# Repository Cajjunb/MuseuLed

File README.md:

# PCB Circuit Specification

## Description
The PCB Circuit Specification project aims to provide detailed specifications and guidelines for designing printed circuit boards (PCBs). This project covers various aspects of PCB design, including component placement, trace routing, and manufacturing considerations. The project is for a Computer Vision application and for the #ART15 fair of computer art.

## Features
- Comprehensive guidelines for PCB component placement
- Detailed trace routing specifications
- Design rules for ensuring signal integrity and minimizing noise
- Manufacturing considerations and best practices
- Sample PCB designs and case studies for reference

## Requirements
- PCB design software (e.g., Eagle, Altium Designer)
- Understanding of electronic components and circuit design principles
- Knowledge of PCB manufacturing processes

## Credits
This project is maintained by Leandro Ramalho Motta Ferreira. If you have any questions or inquiries, please contact [cajjunb@gmail.com].

## License
This project is licensed under the [MIT License](LICENSE)

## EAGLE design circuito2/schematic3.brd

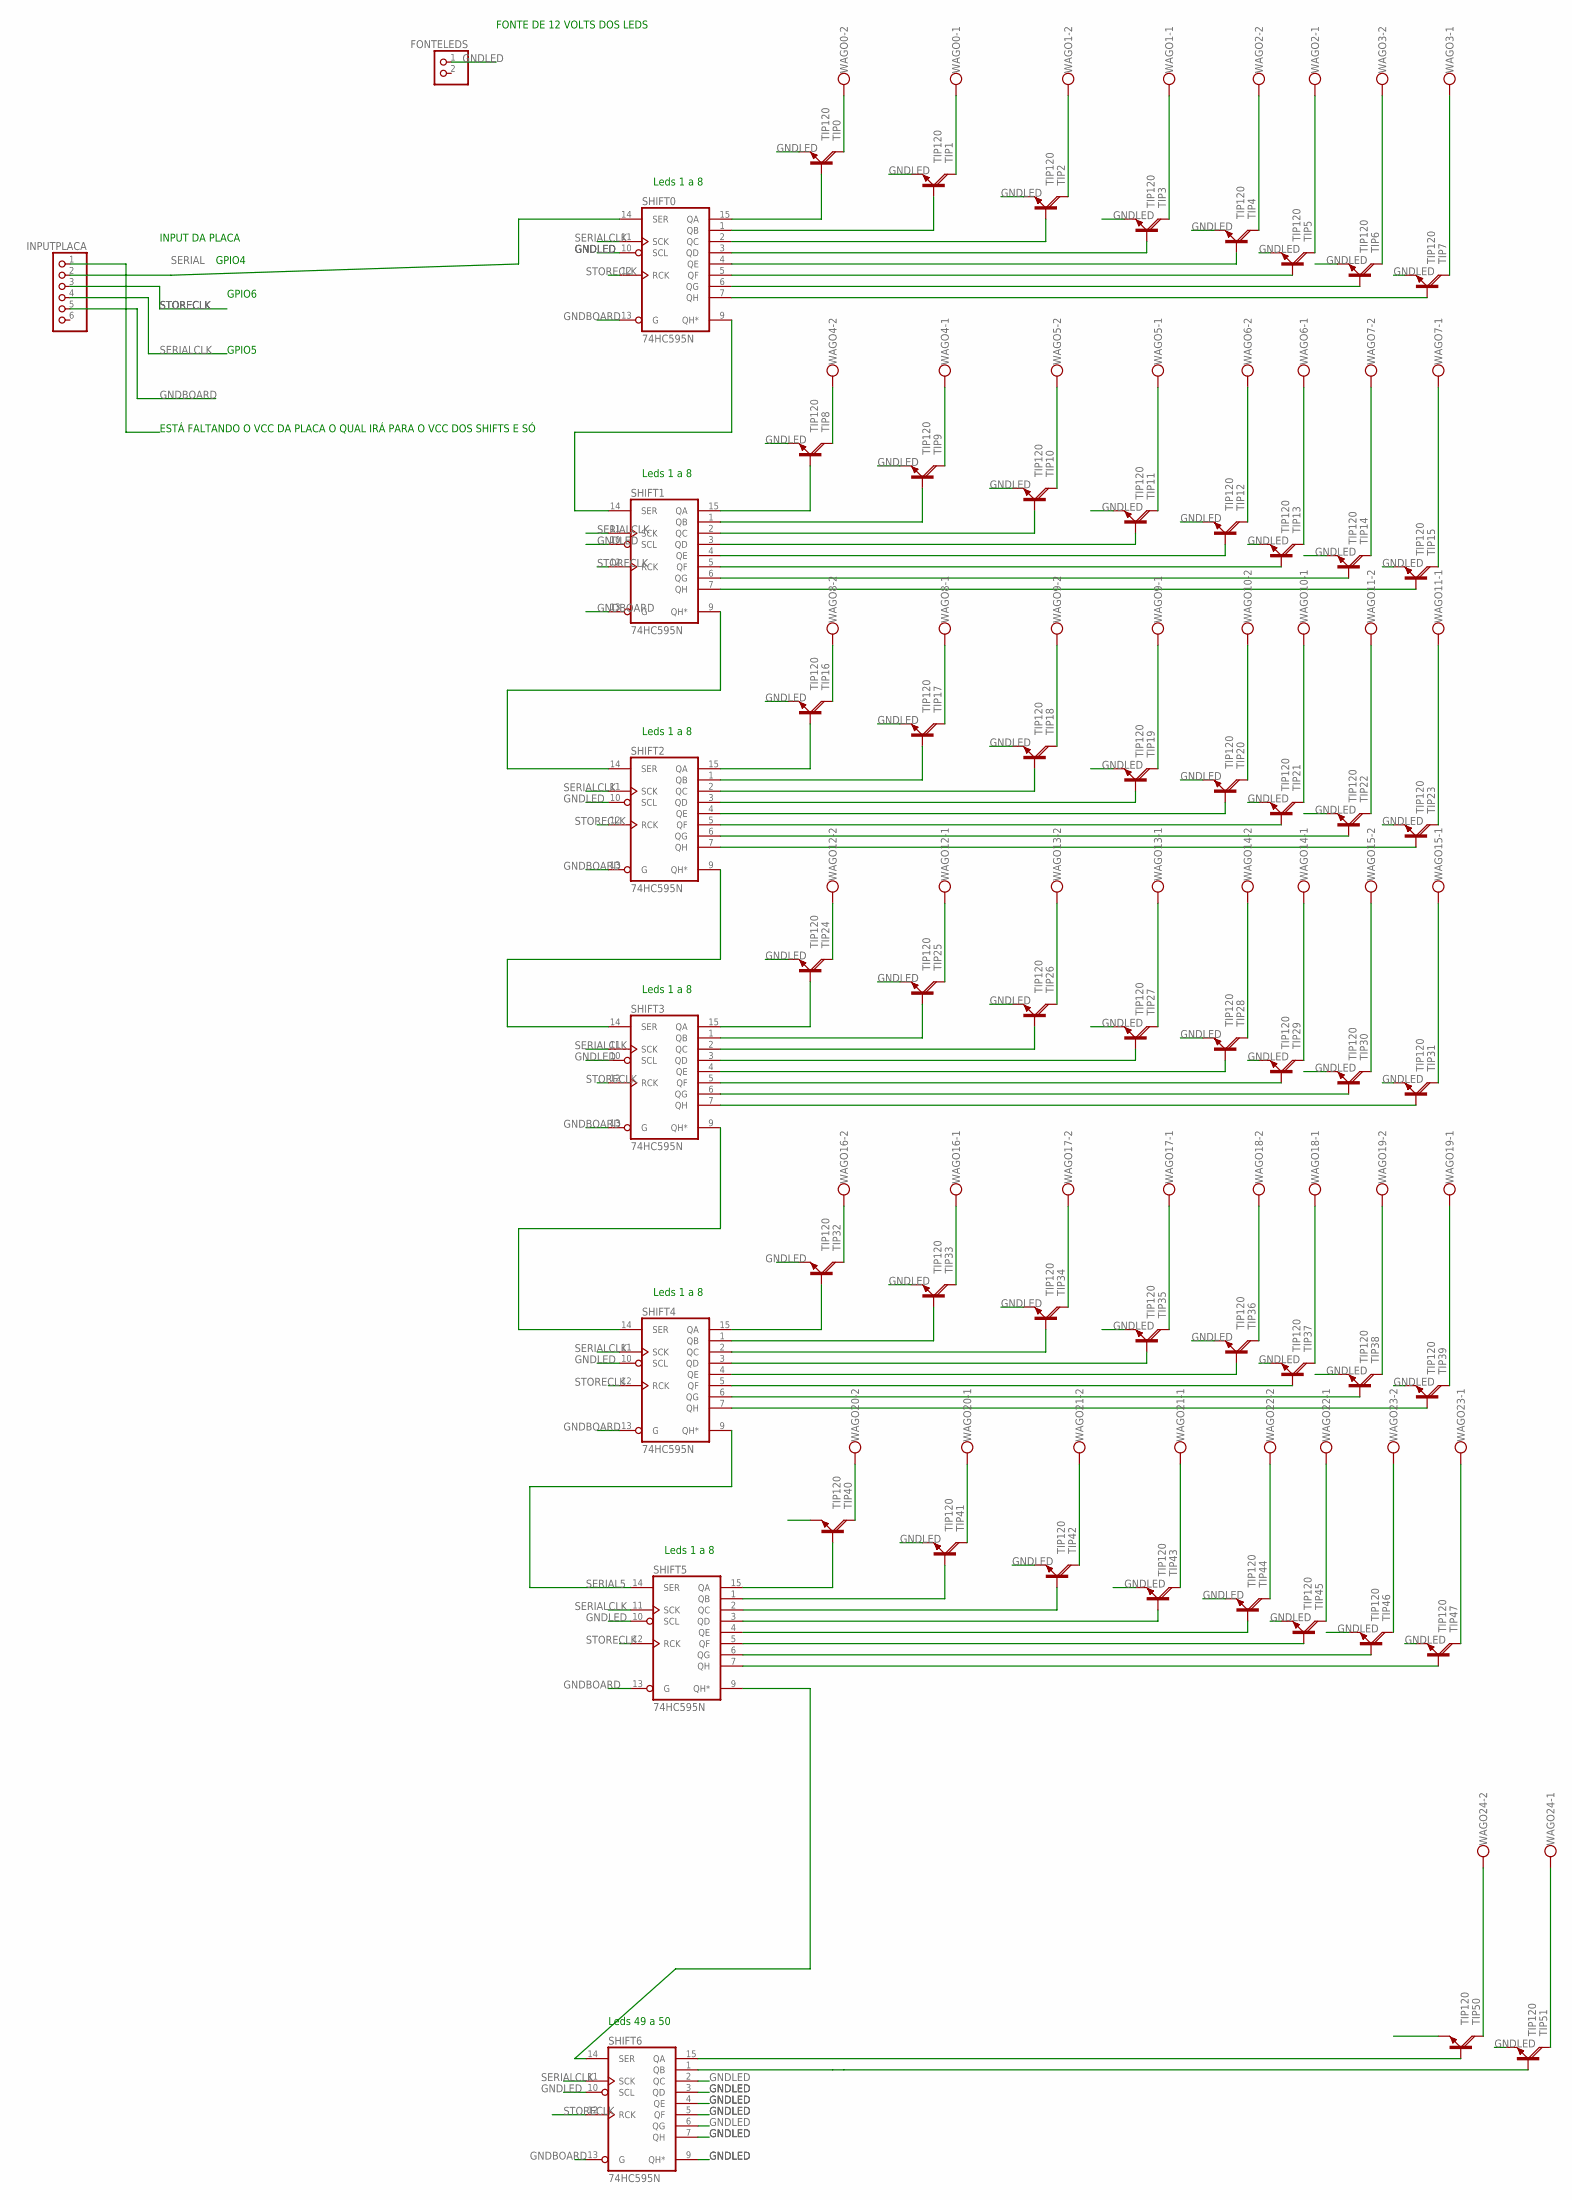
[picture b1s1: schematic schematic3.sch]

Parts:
FONTELEDS: PINHD-1X2; 1X02
INPUTPLACA: PINHD-1X6; 1X06
SHIFT0, SHIFT1, SHIFT2, SHIFT3, SHIFT4, SHIFT5, SHIFT6: 74HC595N; DIL16
TIP0, TIP1, TIP2, TIP3, TIP4, TIP5, TIP6, TIP7, TIP8, TIP9, TIP10, TIP11, TIP12, TIP13, TIP14, TIP15, TIP16, TIP17, TIP18, TIP19, TIP20, TIP21, TIP22, TIP23, TIP24, TIP25, TIP26, TIP27, TIP28, TIP29, TIP30, TIP31, TIP32, TIP33, TIP34, TIP35, TIP36, TIP37, TIP38, TIP39, TIP40, TIP41, TIP42, TIP43, TIP44, TIP45, TIP46, TIP47, TIP50, TIP51: TIP120; TO220AH
WAGO0, WAGO1, WAGO2, WAGO3, WAGO4, WAGO5, WAGO6, WAGO7, WAGO8, WAGO9, WAGO10, WAGO11, WAGO12, WAGO13, WAGO14, WAGO15, WAGO16, WAGO17, WAGO18, WAGO19, WAGO20, WAGO21, WAGO22, WAGO23, WAGO24: W237-102

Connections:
unnamed: SHIFT0.15 (QA), TIP0.B
unnamed: SHIFT0.1 (QB), TIP1.B
unnamed: SHIFT0.2 (QC), TIP2.B
unnamed: SHIFT0.3 (QD), TIP3.B
unnamed: SHIFT0.4 (QE), TIP4.B
unnamed: SHIFT0.5 (QF), TIP5.B
unnamed: SHIFT0.6 (QG), TIP6.B
unnamed: SHIFT0.7 (QH), TIP7.B
unnamed: SHIFT1.15 (QA), TIP8.B
unnamed: SHIFT1.1 (QB), TIP9.B
unnamed 11: SHIFT6.15 (QA), TIP50.B; also elsewhere on the board
unnamed: SHIFT1.2 (QC), TIP10.B
unnamed: SHIFT4.5 (QF), TIP37.B
unnamed: SHIFT1.3 (QD), TIP11.B
unnamed: SHIFT1.4 (QE), TIP12.B
unnamed: SHIFT4.6 (QG), TIP38.B
unnamed: SHIFT1.5 (QF), TIP13.B
unnamed: SHIFT4.7 (QH), TIP39.B
unnamed: SHIFT1.6 (QG), TIP14.B
unnamed: SHIFT5.5 (QF), TIP45.B
unnamed: SHIFT1.7 (QH), TIP15.B
unnamed: TIP8.C, WAGO4.2
unnamed: TIP9.C, WAGO4.1
unnamed: TIP10.C, WAGO5.2
unnamed: TIP11.C, WAGO5.1
unnamed: TIP12.C, WAGO6.2
unnamed: TIP13.C, WAGO6.1
unnamed: TIP14.C, WAGO7.2
unnamed: TIP15.C, WAGO7.1
unnamed: SHIFT2.15 (QA), TIP16.B
unnamed: SHIFT2.1 (QB), TIP17.B
unnamed: SHIFT2.2 (QC), TIP18.B
unnamed: SHIFT2.3 (QD), TIP19.B
unnamed: SHIFT2.4 (QE), TIP20.B
unnamed: SHIFT2.5 (QF), TIP21.B
unnamed: SHIFT2.6 (QG), TIP22.B
unnamed: SHIFT2.7 (QH), TIP23.B
unnamed: TIP16.C, WAGO8.2
unnamed: TIP17.C, WAGO8.1
unnamed: TIP18.C, WAGO9.2
unnamed: TIP19.C, WAGO9.1
unnamed: TIP20.C, WAGO10.2
unnamed: TIP21.C, WAGO10.1
unnamed: SHIFT4.15 (QA), TIP32.B
unnamed: TIP23.C, WAGO11.1
unnamed: SHIFT3.15 (QA), TIP24.B
unnamed: SHIFT3.1 (QB), TIP25.B
unnamed: SHIFT3.2 (QC), TIP26.B
unnamed: SHIFT3.3 (QD), TIP27.B
unnamed: SHIFT3.4 (QE), TIP28.B
unnamed: SHIFT5.6 (QG), TIP46.B
unnamed: SHIFT5.7 (QH), TIP47.B
unnamed: TIP0.C, WAGO0.2
unnamed: SHIFT3.5 (QF), TIP29.B
unnamed: SHIFT3.6 (QG), TIP30.B
unnamed: SHIFT3.7 (QH), TIP31.B
unnamed: TIP24.C, WAGO12.2
unnamed: TIP25.C, WAGO12.1
unnamed: TIP26.C, WAGO13.2
unnamed: SHIFT4.1 (QB), TIP33.B
unnamed: SHIFT4.2 (QC), TIP34.B
unnamed: SHIFT5.9 (QH*), SHIFT6.14 (SER)
unnamed: TIP29.C, WAGO14.1
unnamed: TIP30.C, WAGO15.2
unnamed: TIP31.C, WAGO15.1
unnamed: SHIFT4.3 (QD), TIP35.B
unnamed: SHIFT4.4 (QE), TIP36.B
unnamed: TIP1.C, WAGO0.1
unnamed: TIP2.C, WAGO1.2
unnamed: TIP32.C, WAGO16.2
unnamed: TIP3.C, WAGO1.1
unnamed: TIP33.C, WAGO16.1
unnamed: TIP34.C, WAGO17.2
unnamed: TIP37.C, WAGO18.1
unnamed: TIP38.C, WAGO19.2
unnamed: TIP39.C, WAGO19.1
unnamed: SHIFT5.15 (QA), TIP40.B
unnamed: SHIFT5.1 (QB), TIP41.B
unnamed: SHIFT5.2 (QC), TIP42.B
unnamed: SHIFT5.3 (QD), TIP43.B
unnamed: SHIFT5.4 (QE), TIP44.B
unnamed: TIP40.C, WAGO20.2
unnamed: TIP41.C, WAGO20.1
unnamed: TIP42.C, WAGO21.2
unnamed: TIP45.C, WAGO22.1
unnamed: TIP46.C, WAGO23.2
unnamed: TIP47.C, WAGO23.1
unnamed 88: TIP50.C, WAGO24.2; also elsewhere on the board
unnamed 89: TIP51.C, WAGO24.1; also elsewhere on the board
unnamed 90: SHIFT6.1 (QB), TIP51.B; also elsewhere on the board
unnamed: TIP4.C, WAGO2.2
unnamed: TIP5.C, WAGO2.1
unnamed: TIP6.C, WAGO3.2
unnamed: TIP7.C, WAGO3.1
SERIAL: INPUTPLACA.2, SHIFT0.14 (SER)
SERIAL1: SHIFT0.9 (QH*), SHIFT1.14 (SER)
SERIAL2: SHIFT1.9 (QH*), SHIFT2.14 (SER)
SERIAL3: SHIFT2.9 (QH*), SHIFT3.14 (SER)
SERIAL4: SHIFT3.9 (QH*), SHIFT4.14 (SER)
SERIAL5: SHIFT4.9 (QH*), SHIFT5.14 (SER)
SERIALCLK: INPUTPLACA.4, SHIFT0.11 (SCK), SHIFT1.11 (SCK), SHIFT2.11 (SCK), SHIFT3.11 (SCK), SHIFT4.11 (SCK), SHIFT5.11 (SCK), SHIFT6.11 (SCK)
STORECLK: INPUTPLACA.3, SHIFT0.12 (RCK), SHIFT1.12 (RCK), SHIFT2.12 (RCK), SHIFT3.12 (RCK), SHIFT4.12 (RCK), SHIFT5.12 (RCK), SHIFT6.12 (RCK)
VCC: INPUTPLACA.1, SHIFT0.16 (VCC), SHIFT1.16 (VCC), SHIFT2.16 (VCC), SHIFT3.16 (VCC), SHIFT4.16 (VCC), SHIFT5.16 (VCC), SHIFT6.16 (VCC)
WAGO1: TIP35.C, WAGO17.1
WAGO2: TIP36.C, WAGO18.2
WAGO3: TIP43.C, WAGO21.1
WAGO4: TIP44.C, WAGO22.2
WAGO11: TIP22.C, WAGO11.2
WAGO14: TIP27.C, WAGO13.1
WAGO15: TIP28.C, WAGO14.2

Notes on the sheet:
Leds 1 a 8
Leds 49 a 50
FONTE DE 12 VOLTS DOS LEDS
INPUT DA PLACA
ESTÁ FALTANDO O VCC DA PLACA O QUAL IRÁ PARA O VCC DOS SHIFTS E SÓ
GPIO4
GPIO6
GPIO5

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
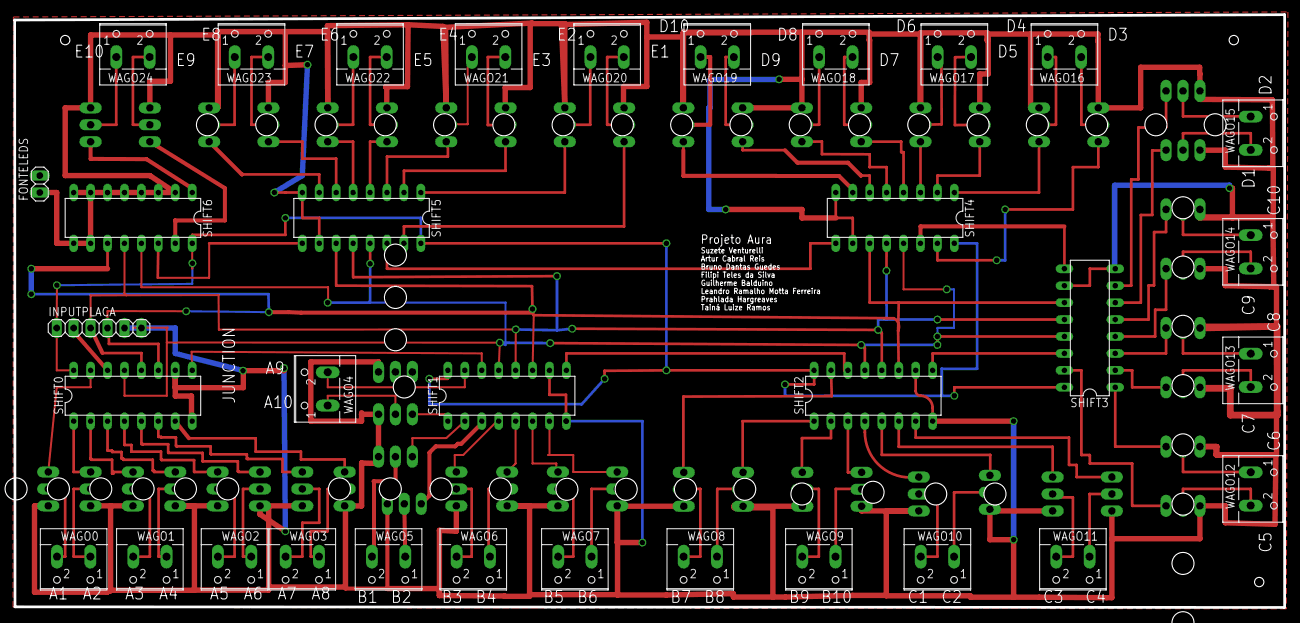
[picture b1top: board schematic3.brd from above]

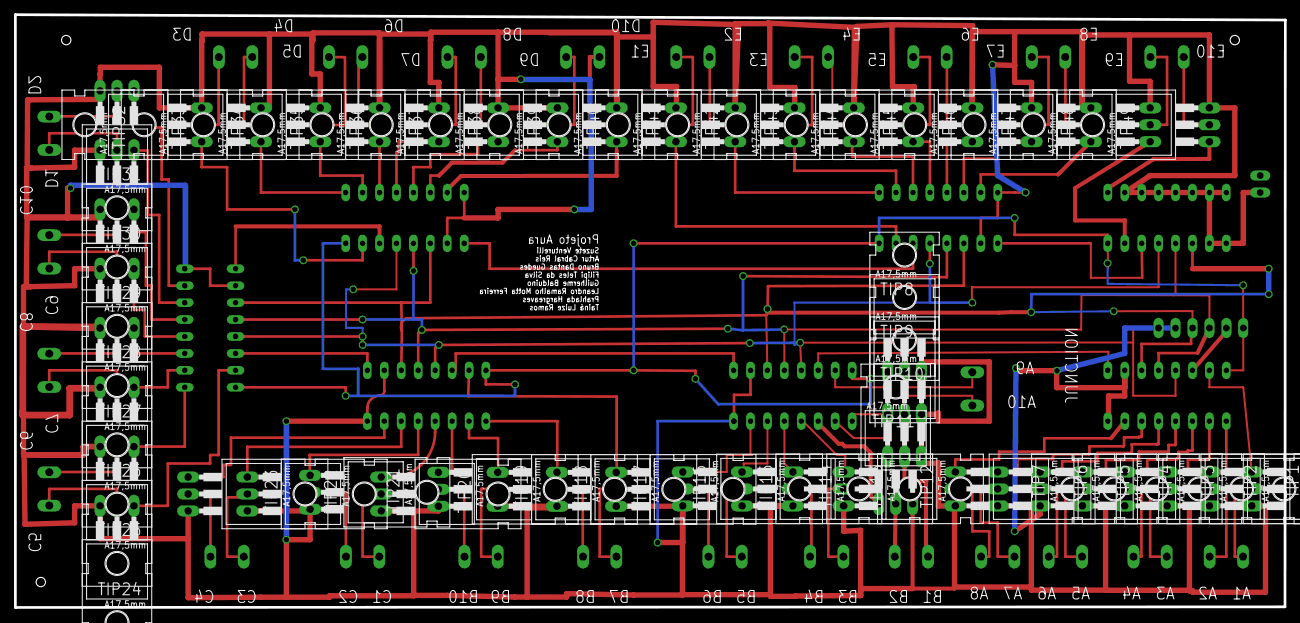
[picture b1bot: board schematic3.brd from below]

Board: 2 copper layers, 190.5 x 88.9 mm, 84 parts (50 on the bottom side), 112 nets.

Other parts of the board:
TIP48, TIP49: TIP120; TO220AH

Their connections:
unnamed 11: TIP48.B; also elsewhere on the board
unnamed 88: TIP48.C; also elsewhere on the board
unnamed 89: TIP49.C; also elsewhere on the board
unnamed 90: TIP49.B; also elsewhere on the board

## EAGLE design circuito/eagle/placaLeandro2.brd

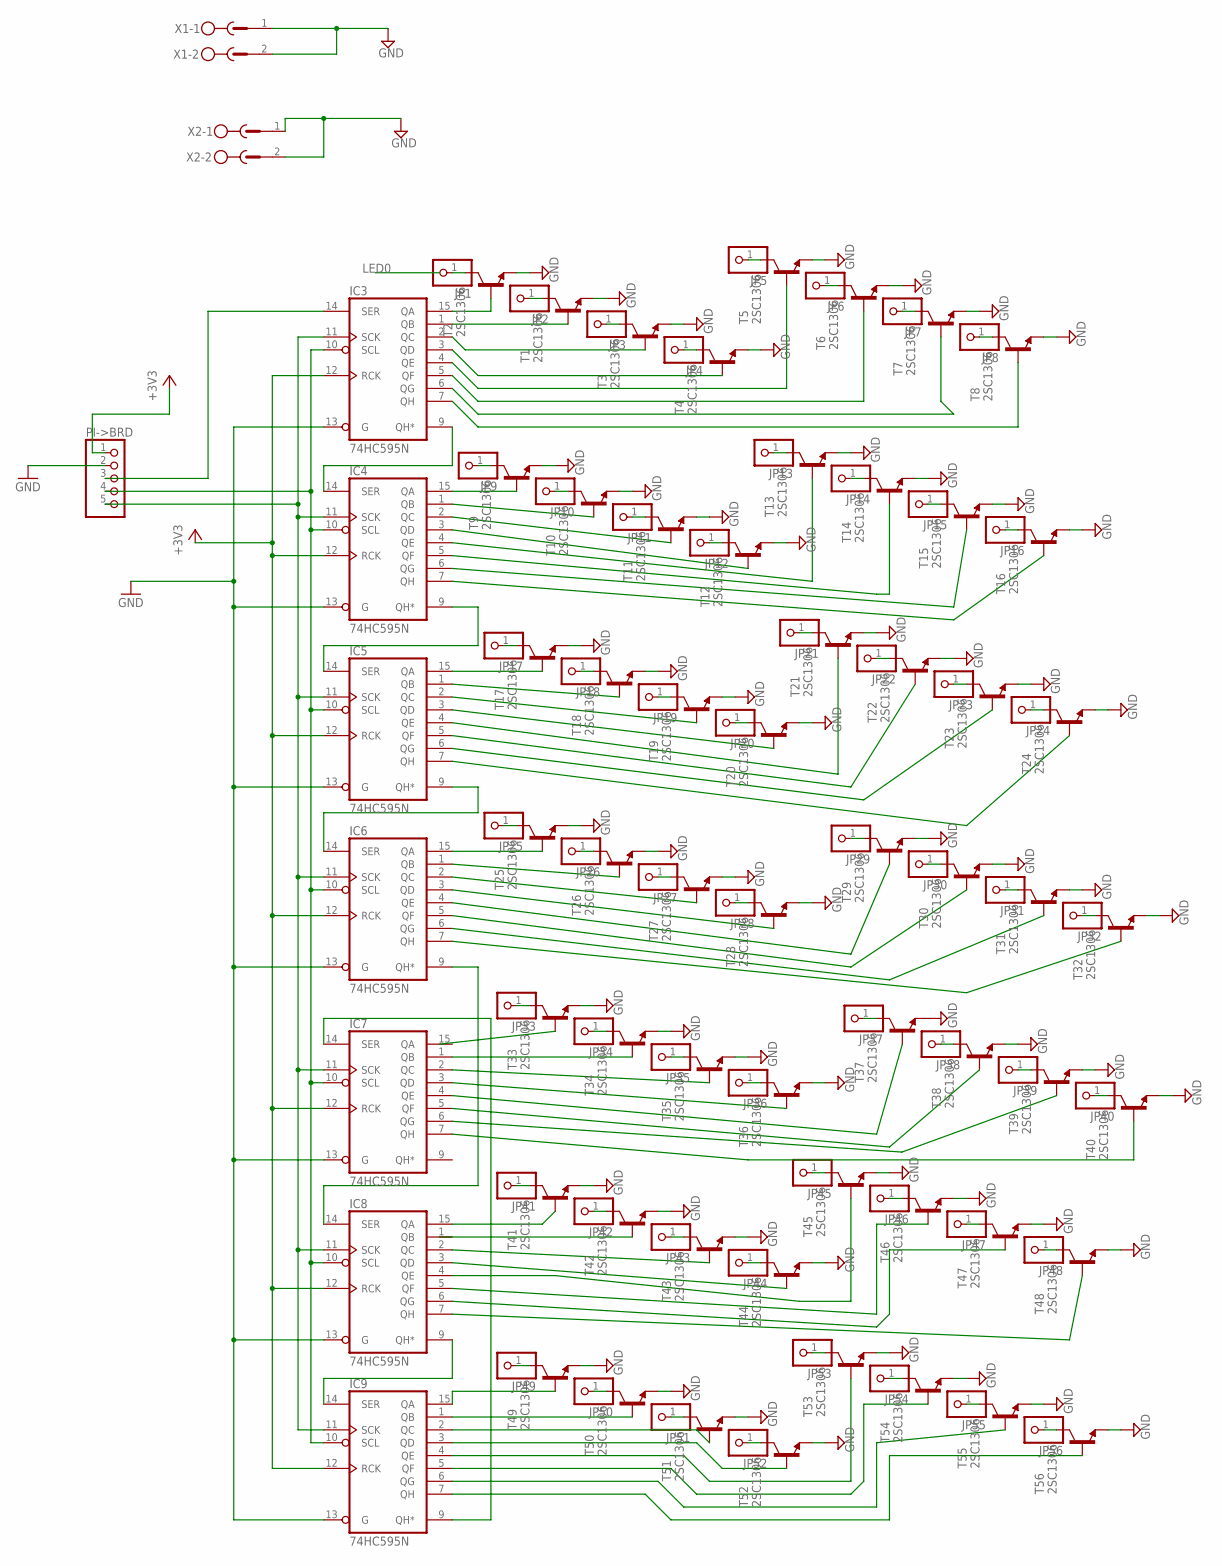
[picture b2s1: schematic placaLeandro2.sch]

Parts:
IC3, IC4, IC5, IC6, IC7, IC8, IC9: 74HC595N; DIL16
JP1, JP2, JP3, JP4, JP5, JP6, JP7, JP8, JP9, JP10, JP11, JP12, JP13, JP14, JP15, JP16, JP17, JP18, JP19, JP20, JP21, JP22, JP23, JP24, JP25, JP26, JP27, JP28, JP29, JP30, JP31, JP32, JP33, JP34, JP35, JP36, JP37, JP38, JP39, JP40, JP41, JP42, JP43, JP44, JP45, JP46, JP47, JP48, JP49, JP50, JP51, JP52, JP53, JP54, JP55, JP56: PINHD-1X1; 1X01
PI->BRD: PINHD-1X5; 1X05
T1, T2, T3, T4, T5, T6, T7, T8, T9, T10, T11, T12, T13, T14, T15, T16, T17, T18, T19, T20, T21, T22, T23, T24, T25, T26, T27, T28, T29, T30, T31, T32, T33, T34, T35, T36, T37, T38, T39, T40, T41, T42, T43, T44, T45, T46, T47, T48, T49, T50, T51, T52, T53, T54, T55, T56: 2SC1306; TO220BV
X1, X2: MSTBV2

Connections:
+3V3: IC3.12 (RCK), IC4.12 (RCK), IC5.12 (RCK), IC6.12 (RCK), IC7.12 (RCK), IC8.12 (RCK), IC9.12 (RCK), PI->BRD.1
GND: IC3.8 (GND), IC3.13 (G), IC4.8 (GND), IC4.13 (G), IC5.8 (GND), IC5.13 (G), IC6.8 (GND), IC6.13 (G), IC7.8 (GND), IC7.13 (G), IC8.8 (GND), IC8.13 (G), IC9.8 (GND), IC9.13 (G), PI->BRD.2, T1.3 (E), T2.3 (E), T3.3 (E), T4.3 (E), T5.3 (E), T6.3 (E), T7.3 (E), T8.3 (E), T9.3 (E), T10.3 (E), T11.3 (E), T12.3 (E), T13.3 (E), T14.3 (E), T15.3 (E), T16.3 (E), T17.3 (E), T18.3 (E), T19.3 (E), T20.3 (E), T21.3 (E), T22.3 (E), T23.3 (E), T24.3 (E), T25.3 (E), T26.3 (E), T27.3 (E), T28.3 (E), T29.3 (E), T30.3 (E), T31.3 (E), T32.3 (E), T33.3 (E), T34.3 (E), T35.3 (E), T36.3 (E), T37.3 (E), T38.3 (E), T39.3 (E), T40.3 (E), T41.3 (E), T42.3 (E), T43.3 (E), T44.3 (E), T45.3 (E), T46.3 (E), T47.3 (E), T48.3 (E), T49.3 (E), T50.3 (E), T51.3 (E), T52.3 (E), T53.3 (E), T54.3 (E), T55.3 (E), T56.3 (E), X1.1, X1.2, X2.1, X2.2
unnamed: IC6.9 (QH*), IC8.14 (SER)
unnamed: IC3.9 (QH*), IC4.14 (SER)
unnamed: IC4.9 (QH*), IC5.14 (SER)
unnamed: IC5.9 (QH*), IC6.14 (SER)
unnamed: IC8.9 (QH*), IC9.14 (SER)
unnamed: IC7.14 (SER), IC9.9 (QH*)
unnamed: IC3.11 (SCK), IC4.11 (SCK), IC5.11 (SCK), IC6.11 (SCK), IC7.11 (SCK), IC8.11 (SCK), IC9.11 (SCK), PI->BRD.5
unnamed: IC3.10 (SCL), IC4.10 (SCL), IC5.10 (SCL), IC6.10 (SCL), IC7.10 (SCL), IC8.10 (SCL), IC9.10 (SCL), PI->BRD.4
unnamed: JP1.1, T2.2 (C)
unnamed: JP2.1, T1.2 (C)
unnamed: JP3.1, T3.2 (C)
unnamed: IC3.14 (SER), PI->BRD.3
unnamed: JP4.1, T4.2 (C)
unnamed: JP5.1, T5.2 (C)
unnamed: JP6.1, T6.2 (C)
unnamed: JP7.1, T7.2 (C)
unnamed: JP8.1, T8.2 (C)
unnamed: JP9.1, T9.2 (C)
unnamed: JP10.1, T10.2 (C)
unnamed: JP11.1, T11.2 (C)
unnamed: JP12.1, T12.2 (C)
unnamed: JP13.1, T13.2 (C)
unnamed: JP14.1, T14.2 (C)
unnamed: JP15.1, T15.2 (C)
unnamed: JP16.1, T16.2 (C)
unnamed: JP17.1, T17.2 (C)
unnamed: JP18.1, T18.2 (C)
unnamed: JP19.1, T19.2 (C)
unnamed: JP20.1, T20.2 (C)
unnamed: JP21.1, T21.2 (C)
unnamed: JP22.1, T22.2 (C)
unnamed: JP23.1, T23.2 (C)
unnamed: JP24.1, T24.2 (C)
unnamed: JP25.1, T25.2 (C)
unnamed: JP26.1, T26.2 (C)
unnamed: JP27.1, T27.2 (C)
unnamed: JP28.1, T28.2 (C)
unnamed: JP29.1, T29.2 (C)
unnamed: JP30.1, T30.2 (C)
unnamed: JP31.1, T31.2 (C)
unnamed: JP32.1, T32.2 (C)
unnamed: JP33.1, T33.2 (C)
unnamed: JP34.1, T34.2 (C)
unnamed: JP35.1, T35.2 (C)
unnamed: JP36.1, T36.2 (C)
unnamed: JP37.1, T37.2 (C)
unnamed: JP38.1, T38.2 (C)
unnamed: JP39.1, T39.2 (C)
unnamed: JP40.1, T40.2 (C)
unnamed: JP41.1, T41.2 (C)
unnamed: JP42.1, T42.2 (C)
unnamed: JP43.1, T43.2 (C)
unnamed: JP44.1, T44.2 (C)
unnamed: JP45.1, T45.2 (C)
unnamed: JP46.1, T46.2 (C)
unnamed: JP47.1, T47.2 (C)
unnamed: JP48.1, T48.2 (C)
unnamed: JP49.1, T49.2 (C)
unnamed: JP50.1, T50.2 (C)
unnamed: JP51.1, T51.2 (C)
unnamed: JP52.1, T52.2 (C)
unnamed: JP53.1, T53.2 (C)
unnamed: JP54.1, T54.2 (C)
unnamed: JP55.1, T55.2 (C)
unnamed: JP56.1, T56.2 (C)
unnamed: IC3.1 (QB), T1.1 (B)
unnamed: IC3.2 (QC), T3.1 (B)
unnamed: IC3.3 (QD), T4.1 (B)
unnamed: IC3.4 (QE), T5.1 (B)
unnamed: IC3.5 (QF), T6.1 (B)
unnamed: IC3.6 (QG), T7.1 (B)
unnamed: IC3.7 (QH), T8.1 (B)
unnamed: IC4.15 (QA), T9.1 (B)
unnamed: IC4.1 (QB), T10.1 (B)
unnamed: IC4.2 (QC), T11.1 (B)
unnamed: IC4.3 (QD), T12.1 (B)
unnamed: IC4.4 (QE), T13.1 (B)
unnamed: IC4.5 (QF), T14.1 (B)
unnamed: IC4.6 (QG), T15.1 (B)
unnamed: IC4.7 (QH), T16.1 (B)
unnamed: IC5.15 (QA), T17.1 (B)
unnamed: IC5.1 (QB), T18.1 (B)
unnamed: IC5.2 (QC), T19.1 (B)
unnamed: IC5.3 (QD), T20.1 (B)
unnamed: IC5.4 (QE), T21.1 (B)
unnamed: IC5.5 (QF), T22.1 (B)
unnamed: IC5.6 (QG), T23.1 (B)
unnamed: IC5.7 (QH), T24.1 (B)
unnamed: IC6.15 (QA), T25.1 (B)
unnamed: IC6.1 (QB), T26.1 (B)
unnamed: IC6.2 (QC), T27.1 (B)
unnamed: IC6.3 (QD), T28.1 (B)
unnamed: IC6.4 (QE), T29.1 (B)
unnamed: IC6.5 (QF), T30.1 (B)
unnamed: IC6.6 (QG), T31.1 (B)
unnamed: IC6.7 (QH), T32.1 (B)
unnamed: IC7.15 (QA), T33.1 (B)
unnamed: IC7.1 (QB), T34.1 (B)
unnamed: IC7.2 (QC), T35.1 (B)
unnamed: IC7.3 (QD), T36.1 (B)
unnamed: IC7.4 (QE), T37.1 (B)
unnamed: IC7.5 (QF), T38.1 (B)
unnamed: IC7.6 (QG), T39.1 (B)
unnamed: IC7.7 (QH), T40.1 (B)
unnamed: IC8.15 (QA), T41.1 (B)
unnamed: IC8.1 (QB), T42.1 (B)
unnamed: IC8.2 (QC), T43.1 (B)
unnamed: IC8.3 (QD), T44.1 (B)
unnamed: IC8.4 (QE), T45.1 (B)
unnamed: IC8.5 (QF), T46.1 (B)
unnamed: IC8.6 (QG), T47.1 (B)
unnamed: IC8.7 (QH), T48.1 (B)
unnamed: IC9.15 (QA), T49.1 (B)
unnamed: IC9.1 (QB), T50.1 (B)
unnamed: IC9.2 (QC), T51.1 (B)
unnamed: IC9.3 (QD), T52.1 (B)
unnamed: IC9.4 (QE), T53.1 (B)
unnamed: IC9.5 (QF), T54.1 (B)
unnamed: IC9.6 (QG), T55.1 (B)
unnamed: IC9.7 (QH), T56.1 (B)
unnamed: IC3.15 (QA), T2.1 (B)
VCC: IC3.16 (VCC), IC4.16 (VCC), IC5.16 (VCC), IC6.16 (VCC), IC7.16 (VCC), IC8.16 (VCC), IC9.16 (VCC)

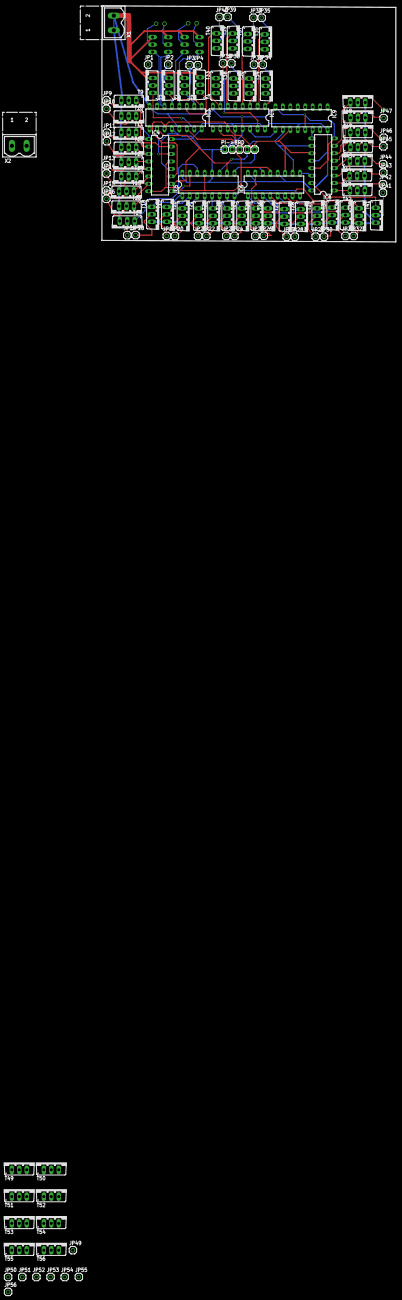
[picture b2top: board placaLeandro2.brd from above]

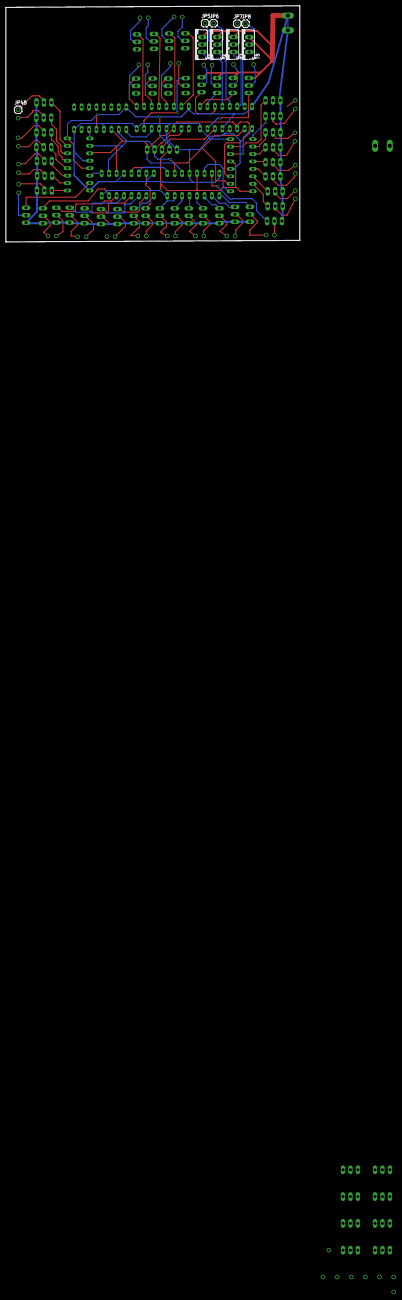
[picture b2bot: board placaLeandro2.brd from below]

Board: 2 copper layers, 100.3 x 80.5 mm, 122 parts (9 on the bottom side), 124 nets.

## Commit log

2016-06-24 primeiro commit com o exemplo
2016-06-24 aprendi como funciona a difusao e modifiquei
2016-07-03 3x3 raio de difusao
2016-07-14 reconsertei e comecando a fazer o farejamento
2016-07-16 Resolvendo conflitos de programacao Concorrente
2016-08-02 Voltando de ferias, movimento randomico
2016-08-02 terminando o 3x3 funcionando
2016-08-02 resolvi um erro
2016-08-10 comecando a camera
2016-08-10 mudei resolucao e ficou melhor
2016-08-10 Errei e voltei agora com a camera aparecendo
2016-08-15 consegui fazer que a camera detecte diferenca entre a camera e preto
2016-08-15 tracking funcionando
2016-08-19 commit para testar no raspberry
2016-08-26 Resolvi o negocio 5000 ms
2016-08-26 versao que funciona ALgo no raspberry
2016-08-29 FUNCIONANDO RASPBERRY POHA
2016-08-29 tentando outras portas do raspb
2016-08-30 shift funcionando
2016-09-05 comecando o hardware
2016-09-05 mudei as pastas
2016-09-12 fiz o primeiro sketch
2016-09-14 circuito verso dia 12
2016-09-14 coloquei os transistores em todas as saidas
2016-09-16 tentando fazer o circuito
2016-09-21 circuito Finalizado falta a alimentacao dos leds
2016-09-21 Circuito 2 com a bateria ja
2016-09-21 Circuito feito
2016-09-26 schematic eagle!
2016-09-26 segunda linha de tips
2016-09-26 circuito 2 denovo
2016-09-26 circuito 3 feito
2016-09-27 terminando o penultimo circuito
2016-09-29 teste de interface funcionando e o totem ta aqui
2016-09-30 VERSAO FINAL DO MUSEU NACIONAL DIA 4 de outubro de 2016
2017-03-23 terminando o circuito 2
2017-03-23 to no shift 3
2017-03-23 parei da quitna
2017-03-26 terminei quase
2017-03-26 criei o outline da placa
2017-03-26 endireitei as margens
2017-03-26 apos calculo 22cm de largura
2017-03-27 diminui para 20 cm
2017-03-27 resolvido tamanho da placa
2017-03-28 botei a logo e fiz uma verificacao de design
2017-04-06 resolvendo a parte da impressao
2017-04-06 pequenos consertos
2017-04-11 Placa pos correcoes do professor do sg 11
2017-04-11 mais um detalhe feito separando as ilhas
2017-04-11 correçaoprahlada
2017-04-11 correcoes dos airwires
2017-04-13 placa versao final com ilhas maneiras
2017-05-03 nao sei
2017-06-08 uma alteração grande fazendo teste versão 2
